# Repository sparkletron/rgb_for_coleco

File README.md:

# RGB for Colecovision
### Schematic and PCB for production of a sub rf replacement board that is Genesis 9 pin compatible.

---

  author: Jay Convertino

  date: 2023.07.10

  details: Converts internal YPbPr to RGB to Pound Genesis cable (Genesis compatible outputs)

  license: MIT

---

## LICENSE
  - All files related to or generated from the KiCAD source fall under the MIT license.
  - All files generated by me, Jay Convertino, fall under the MIT license.
  - All files from other sources fall under the license of their specification.

## RELEASE VERSIONS
### Current
  - 0.5 BETA

### Past
  - DEV

## Intro

  This circuit is a replacment for the sub rf board of the original colecovison.

## SOURCES
### RGB conversion
  - TMS RGB : https://tms-rgb.com/ : Nicholas Piegdon

  Special thanks to Nicholas Piegdon. For using the TI YPbPr chip in his design and coming up with the resistor values to obtain proper color
  balance from a TMS9928. This circuit uses a different method for the too much blue. In this case it switches to a sample generated internally by the coleco that is also used to set the DC offset during sync. Also the driver is based on being compatible with the sega
  genesis. This works well with the Pound cable, yes its kinda crap, but its cheap and provides a baseline from which you can only go up.

## REQUIREMENTS
  - KiCAD v7.X

## BUILD TIPS
  This design is made so anyone can build this. You may send it out to a fab house, you may use a PCB mill, or even etch it.
  This is possible since the components can serve as the plated through hole. Other holes can simply have a solid piece of
  wire inserted and soldered to complete the connection (excess resistor leads is a great option).

  Recommend removing the Y, Pb, Pr inductors that are inline if they are there. They will cause color smearing.

  Output composite resistors and cap are optional, can replace the resistor connecting the output to the inverting input with a jumper.
  If no gain is wanted.

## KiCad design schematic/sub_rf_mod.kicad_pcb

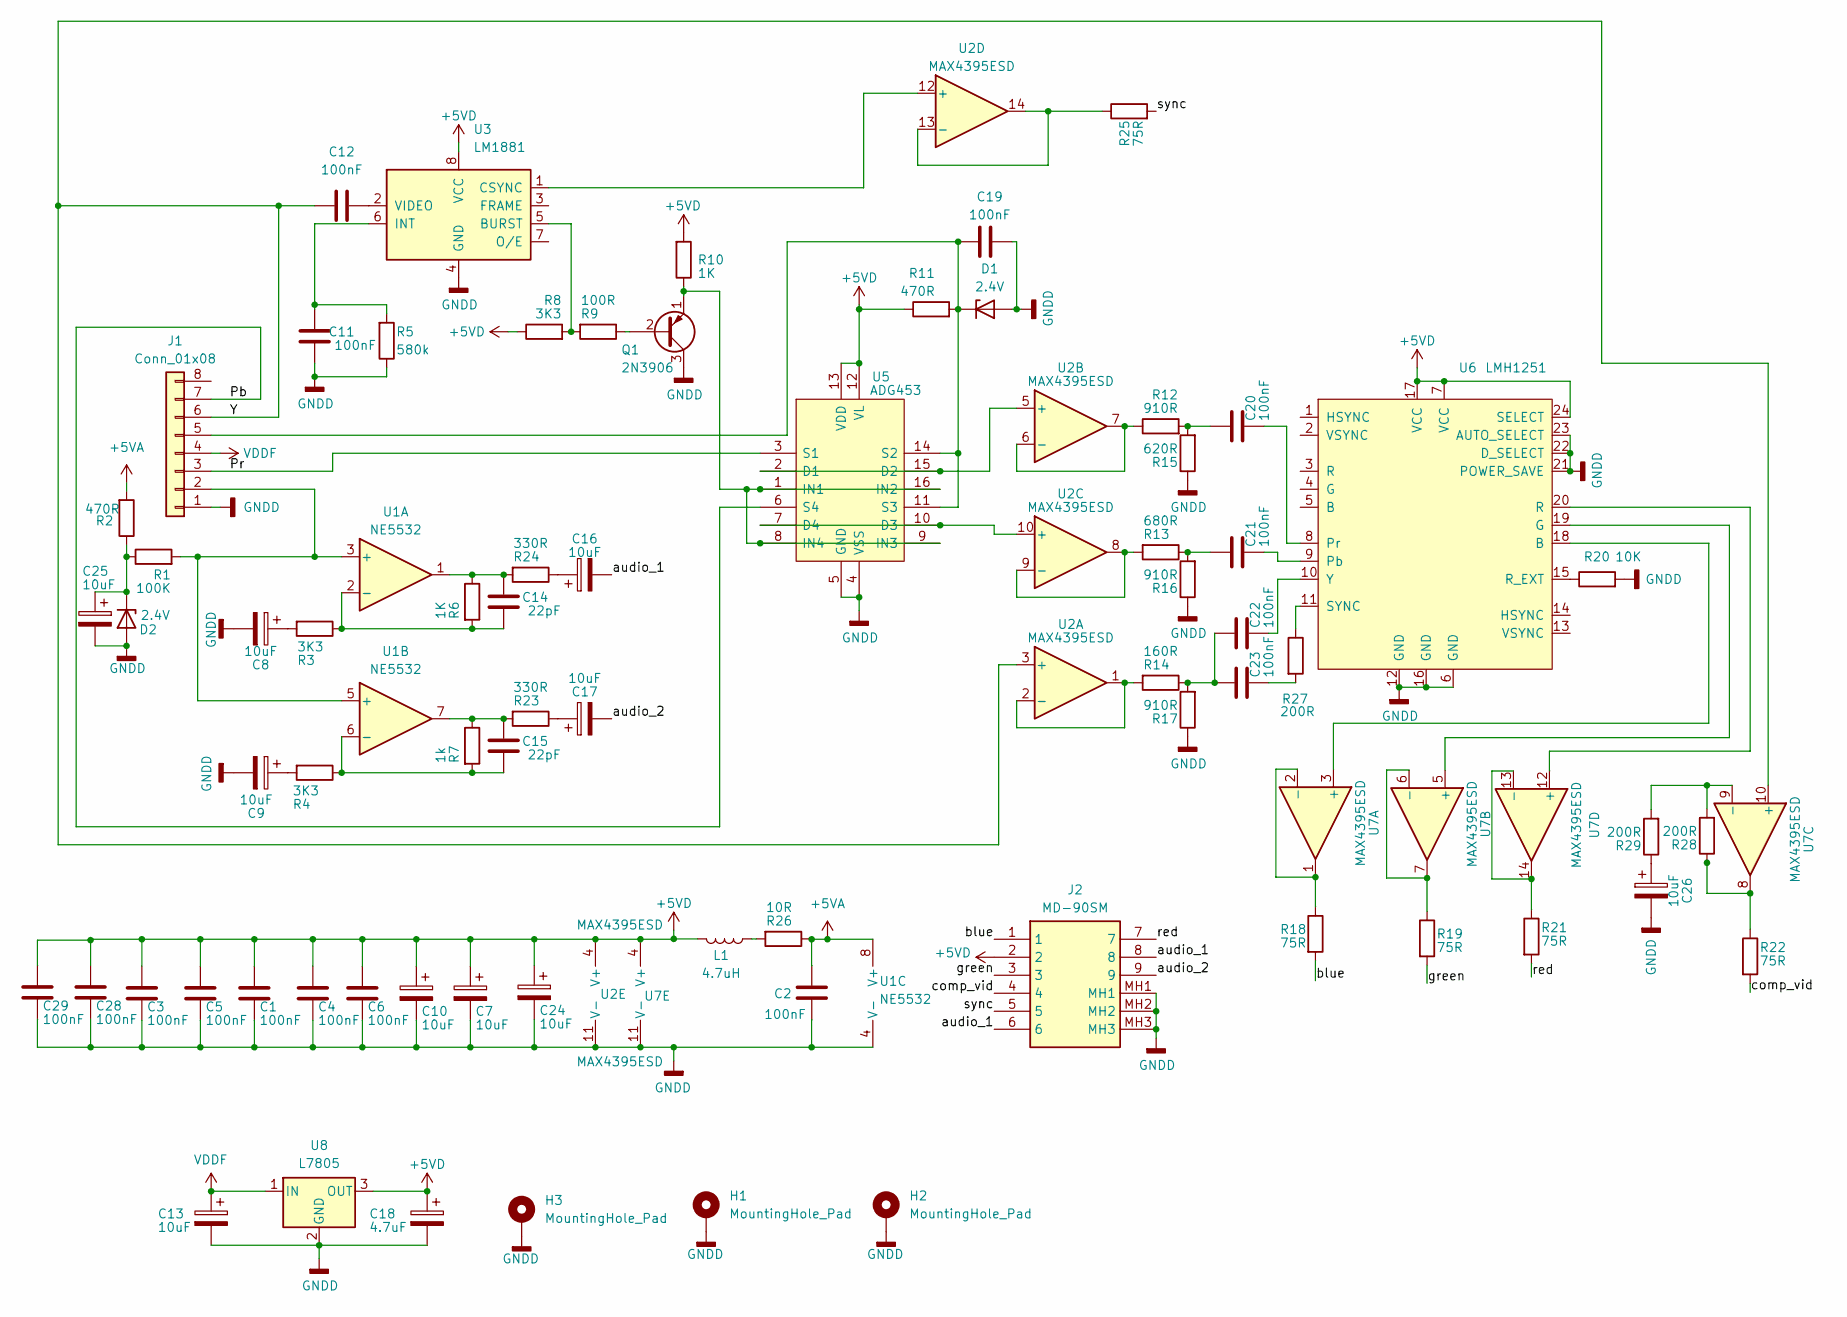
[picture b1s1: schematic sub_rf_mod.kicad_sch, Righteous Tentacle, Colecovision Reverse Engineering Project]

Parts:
C1, C2, C3, C4, C5, C6, C11, C12, C19, C20, C21, C22, C23, C28, C29: 100nF; C_Disc_D5.0mm_W2.5mm_P5.00mm
C7, C8, C9, C10, C13, C16, C17, C25, C26: 10uF; CP_Radial_D4.0mm_P2.00mm
C14, C15: 22pF; C_Disc_D5.0mm_W2.5mm_P5.00mm
C18: 4.7uF; CP_Radial_D4.0mm_P2.00mm
C24: 10uF; CP_Radial_Tantal_D4.5mm_P2.50mm
D1, D2: 2.4V; D_DO-35_SOD27_P7.62mm_Horizontal
H1, H2: MountingHole_Pad; MountingHole_2.2mm_M2_DIN965_Pad
H3: MountingHole_Pad; MountingHole_3mm_Pad
J1: Conn_01x08; PinHeader_1x08_P2.54mm_Vertical
J2: MD-90SM; MD90SM; Manufacturer_Part_Number MD-90SM; Mouser Part Number 490-MD-90SM
L1: 4.7uH; L_Axial_L7.0mm_D3.3mm_P10.16mm_Horizontal_Fastron_MICC
Q1: 2N3906; TO-92_Wide
R1: 100K; R_Axial_DIN0207_L6.3mm_D2.5mm_P7.62mm_Horizontal
R2, R11: 470R; R_Axial_DIN0207_L6.3mm_D2.5mm_P7.62mm_Horizontal
R3, R4, R8: 3K3; R_Axial_DIN0207_L6.3mm_D2.5mm_P7.62mm_Horizontal
R5: 580k; R_Axial_DIN0207_L6.3mm_D2.5mm_P7.62mm_Horizontal
R6, R10: 1K; R_Axial_DIN0207_L6.3mm_D2.5mm_P7.62mm_Horizontal
R7: 1k; R_Axial_DIN0207_L6.3mm_D2.5mm_P7.62mm_Horizontal
R9: 100R; R_Axial_DIN0207_L6.3mm_D2.5mm_P7.62mm_Horizontal
R12, R16, R17: 910R; R_Axial_DIN0207_L6.3mm_D2.5mm_P7.62mm_Horizontal
R13: 680R; R_Axial_DIN0207_L6.3mm_D2.5mm_P7.62mm_Horizontal
R14: 160R; R_Axial_DIN0207_L6.3mm_D2.5mm_P7.62mm_Horizontal
R15: 620R; R_Axial_DIN0207_L6.3mm_D2.5mm_P7.62mm_Horizontal
R18, R19, R21, R22, R25: 75R; R_Axial_DIN0207_L6.3mm_D2.5mm_P7.62mm_Horizontal
R20: 10K; R_Axial_DIN0207_L6.3mm_D2.5mm_P10.16mm_Horizontal
R23, R24: 330R; R_Axial_DIN0207_L6.3mm_D2.5mm_P7.62mm_Horizontal
R26: 10R; R_Axial_DIN0207_L6.3mm_D2.5mm_P7.62mm_Horizontal
R27, R28, R29: 200R; R_Axial_DIN0207_L6.3mm_D2.5mm_P7.62mm_Horizontal
U1: NE5532; SOIC-8_3.9x4.9mm_P1.27mm
U2, U7: MAX4395ESD; SO-14_3.9x8.65mm_P1.27mm
U3: LM1881; SOIC-8_3.9x4.9mm_P1.27mm
U5: ADG453; SOIC-16_3.9x9.9mm_P1.27mm
U6: LMH1251; TSSOP-24_4.4x7.8mm_P0.65mm
U8: L7805; TO-220-3_Vertical

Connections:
+5VA: C2.2, R2.2, R26.1, U1.8 (V+)
+5VD: C1.2, C3.2, C4.2, C5.2, C6.2, C7.1, C10.1, C18.1, C24.1, C28.2, C29.2, J2.2, L1.2, R8.1, R10.2, R11.1, U2.4 (V+), U3.8 (VCC), U5.12 (VL), U5.13 (VDD), U6.7 (VCC), U6.17 (VCC), U6.24 (SELECT), U7.4 (V+), U8.3 (OUT)
/Pb: J1.7, U5.6 (S4)
/Pr: J1.3, U5.3 (S1)
/Y: C12.1, J1.6, U2.3 (+), U7.10 (+)
/audio_1: C16.2, J2.6, J2.8
/audio_2: C17.2, J2.9
/blue: J2.1, R18.2
/comp_vid: J2.4, R22.2
/green: J2.3, R19.2
/red: J2.7, R21.2
/sync: J2.5, R25.2
GNDD: C1.1, C2.1, C3.1, C4.1, C5.1, C6.1, C7.2, C8.2, C9.2, C10.2, C11.1, C13.2, C18.2, C19.2, C24.2, C25.2, C26.2, C28.1, C29.1, D1.2 (A), D2.2 (A), H1.1, H2.1, H3.1, J1.1, J2.MH1, J2.MH2, J2.MH3, Q1.3 (C), R5.1, R15.1, R16.1, R17.1, R20.2, U1.4 (V-), U2.11 (V-), U3.4 (GND), U5.4 (VSS), U5.5 (GND), U6.6 (GND), U6.12 (GND), U6.16 (GND), U6.21 (POWER_SAVE), U6.22 (D_SELECT), U6.23 (AUTO_SELECT), U7.11 (V-), U8.2 (GND)
unnamed: C8.1, R3.2
unnamed: C9.1, R4.2
unnamed: C14.2, R6.1, R24.2, U1.1
unnamed: C15.2, R7.1, R23.2, U1.7
unnamed: C16.1, R24.1
unnamed: C17.1, R23.1
unnamed: C20.2, R12.2, R15.2
unnamed: C21.2, R13.1, R16.2
unnamed: C22.2, C23.2, R14.1, R17.2
unnamed: C23.1, R27.2
unnamed: C26.1, R29.1
unnamed: C19.1, D1.1 (K), J1.5, R11.2, U5.11 (S3), U5.14 (S2)
unnamed: C25.1, D2.1 (K), R1.1, R2.1
unnamed: J1.2, R1.2, U1.3 (+), U1.5 (+)
unnamed: L1.1, R26.2
unnamed: Q1.2 (B), R9.1
unnamed: Q1.1 (E), R10.1, U5.1 (IN1), U5.8 (IN4), U5.9 (IN3), U5.16 (IN2)
unnamed: R22.1, R28.1, U7.8
unnamed: C14.1, R3.1, R6.2, U1.2 (-)
unnamed: C15.1, R4.1, R7.2, U1.6 (-)
unnamed: R14.2, U2.1, U2.2 (-)
unnamed: U2.5 (+), U5.2 (D1), U5.15 (D2)
unnamed: R12.1, U2.6 (-), U2.7
unnamed: U2.10 (+), U5.7 (D4), U5.10 (D3)
unnamed: R13.2, U2.8, U2.9 (-)
unnamed: U2.12 (+), U3.1 (CSYNC)
unnamed: R25.1, U2.13 (-), U2.14
unnamed: R8.2, R9.2, U3.5 (BURST)
unnamed: C11.2, R5.2, U3.6 (INT)
unnamed: C12.2, U3.2 (VIDEO)
unnamed: C21.1, U6.9 (Pb)
unnamed: C20.1, U6.8 (Pr)
unnamed: R20.1, U6.15 (R_EXT)
unnamed: R27.1, U6.11 (SYNC)
unnamed: C22.1, U6.10 (Y)
unnamed: U6.18 (B), U7.3 (+)
unnamed: R18.1, U7.1, U7.2 (-)
unnamed: U6.19 (G), U7.5 (+)
unnamed: R19.1, U7.6 (-), U7.7
unnamed: R28.2, R29.2, U7.9 (-)
unnamed: U6.20 (R), U7.12 (+)
unnamed: R21.1, U7.13 (-), U7.14
VDDF: C13.1, J1.4, U8.1 (IN)

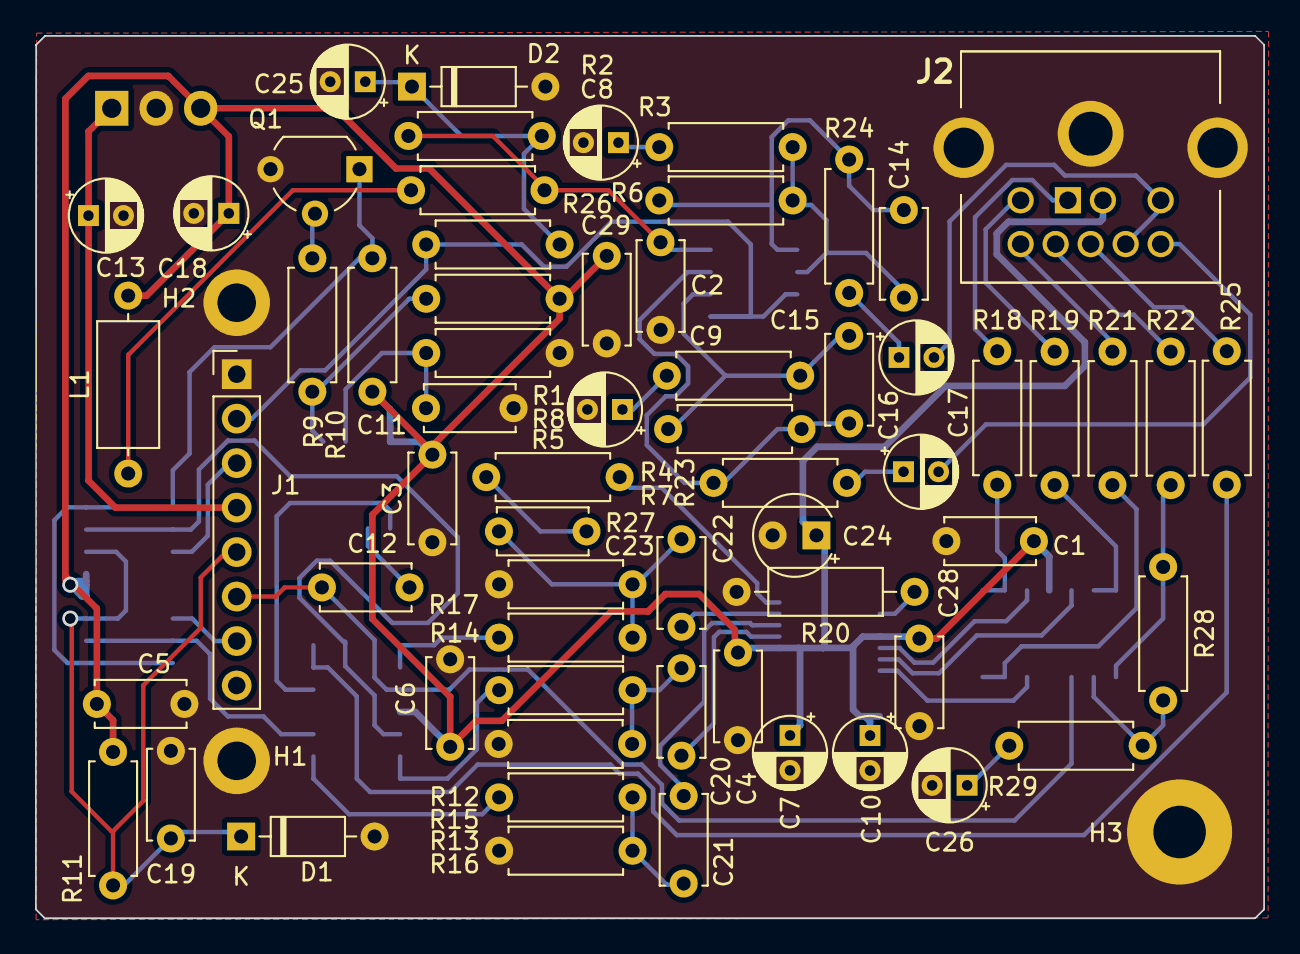
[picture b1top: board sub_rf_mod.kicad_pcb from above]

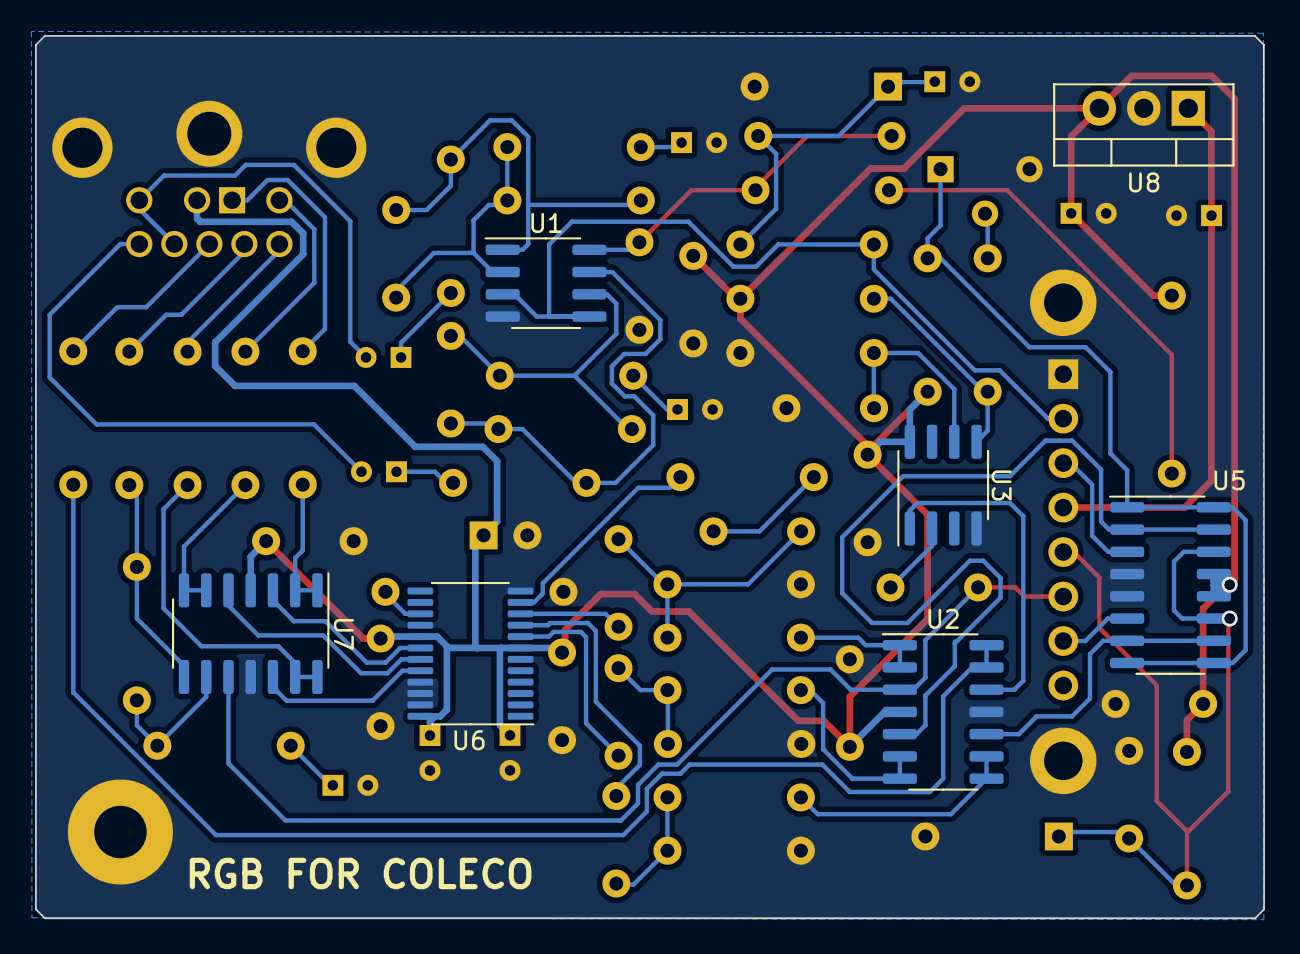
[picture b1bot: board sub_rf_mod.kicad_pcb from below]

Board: 2 copper layers, 70.1 x 50.4 mm, 73 parts (7 on the bottom side), 56 nets.

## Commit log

2023-07-11 cleanpu readme title
2024-03-25 fixed for github
2025-06-28 add schematic
